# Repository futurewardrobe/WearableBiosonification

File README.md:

# WearableBiosonification
Wearable bio-data sonification device

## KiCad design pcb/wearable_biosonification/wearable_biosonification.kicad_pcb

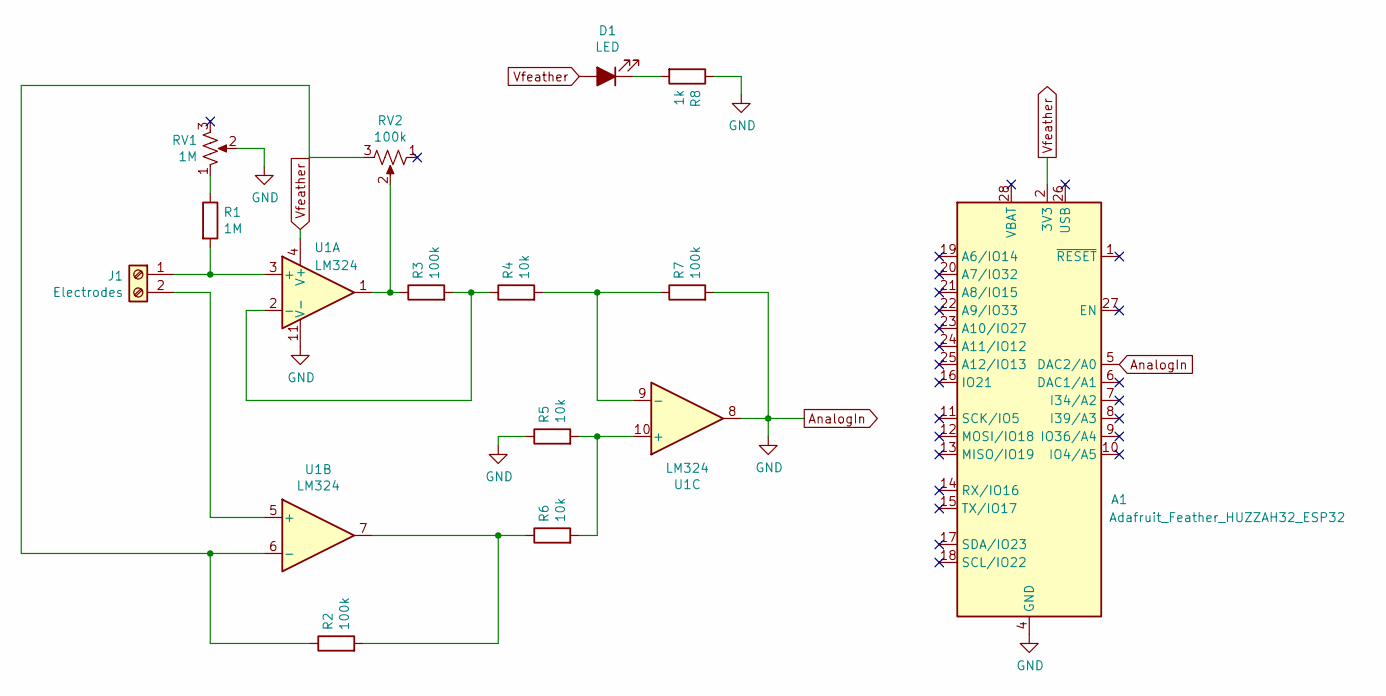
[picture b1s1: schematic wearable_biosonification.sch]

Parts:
A1: Adafruit_Feather_HUZZAH32_ESP32; Adafruit_Feather
D1: LED; LED_0805_2012Metric_Pad1.15x1.40mm_HandSolder
J1: Electrodes; TerminalBlock_Phoenix_PT-1,5-2-3.5-H_1x02_P3.50mm_Horizontal
R1: 1M; R_0805_2012Metric_Pad1.20x1.40mm_HandSolder
R2, R3, R7: 100k; R_0805_2012Metric_Pad1.20x1.40mm_HandSolder
R4, R5, R6: 10k; R_0805_2012Metric_Pad1.20x1.40mm_HandSolder
R8: 1k; R_0805_2012Metric_Pad1.20x1.40mm_HandSolder
RV1: 1M; Potentiometer_Bourns_3386X_Horizontal
RV2: 100k; Potentiometer_Bourns_3386X_Horizontal
U1: LM324; SOIC-14_3.9x8.7mm_P1.27mm

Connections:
AnalogIn: A1.4 (GND), A1.5 (DAC2/A0), R5.1, R7.2, R8.1, RV1.2, U1.8, U1.11 (V-)
unnamed: D1.1 (K), R8.2
unnamed: J1.1, R1.2, U1.3 (+)
unnamed: J1.2, U1.5 (+)
unnamed: R1.1, RV1.1
unnamed: R2.1, RV2.3, U1.6 (-)
unnamed: R2.2, R6.1, U1.7
unnamed: R3.1, RV2.2, U1.1
unnamed: R3.2, R4.1, U1.2 (-)
unnamed: R4.2, R7.1, U1.9 (-)
unnamed: R5.2, R6.2, U1.10 (+)
Vfeather: A1.2 (3V3), D1.2 (A), U1.4 (V+)

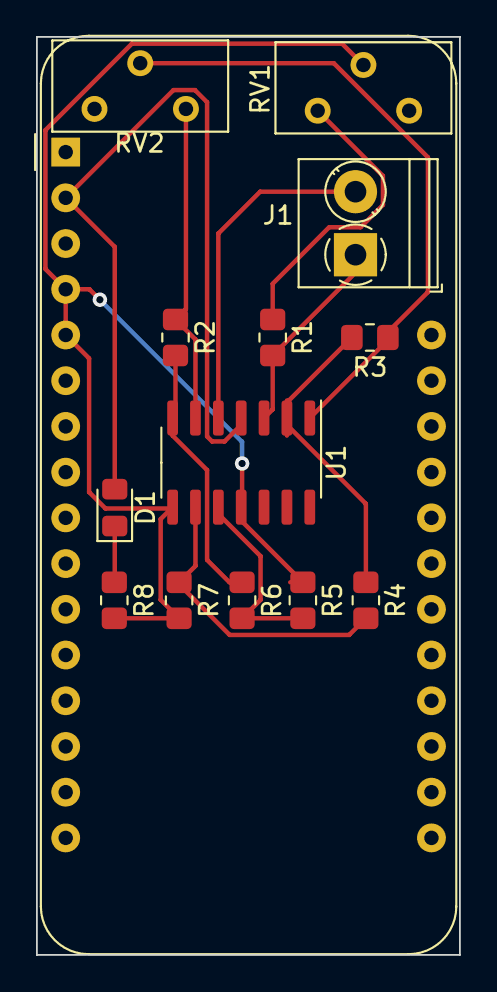
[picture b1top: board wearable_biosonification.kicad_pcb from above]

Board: 2 copper layers, 23.5 x 51.0 mm, 14 parts (0 on the bottom side), 12 nets.

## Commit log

2020-12-08 added kicad files
2020-12-08 added arduino code
2020-12-08 added processing code
2020-12-08 added constants to adjust the size of the graph
2020-12-08 updated BOM
2020-12-08 removed testpoints + added LED
2020-12-09 added install script for raspberry pi
2020-12-09 added wpa_supplicant.conf template
2020-12-09 adding dhcpcd.conf
2020-12-09 install sets up static ip on network
2020-12-09 adding processing sketch autostart service
2020-12-09 updated service file
2020-12-09 updated unit file
2020-12-09 corrected spelling
2020-12-09 finished auto start processing sketch
2020-12-10 added inital puredata files
2020-12-10 hiding cursor in processing sketch
2020-12-10 added deken as dependency to install.sh
2020-12-10 added pd externals and osc test
2020-12-10 installing pd externals via repo + adding start servvice
2020-12-10 fullscreen = false
2020-12-10 starting pd with -nogui
2020-12-29 added gerber files
2021-01-22 added pd files
2021-01-22 changed puredata start file
2021-01-22 set processing to fullscreen
2021-01-30 added sound control sliders
2021-01-30 adde controlP5 to install script
2021-01-30 changed audio output dev number
2021-01-30 updated gerber files
2021-01-30 updated gitignore
2021-02-27 added fauxsc_sender arduino sketch
    fauxsc_sender is mock version of the sensor
2021-03-05 fixed volume issue
2021-03-09 updated mock_sender for processing
